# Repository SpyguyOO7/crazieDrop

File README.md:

# PCB for little electromagnet drop mech
## SChematic

## Model + Layout

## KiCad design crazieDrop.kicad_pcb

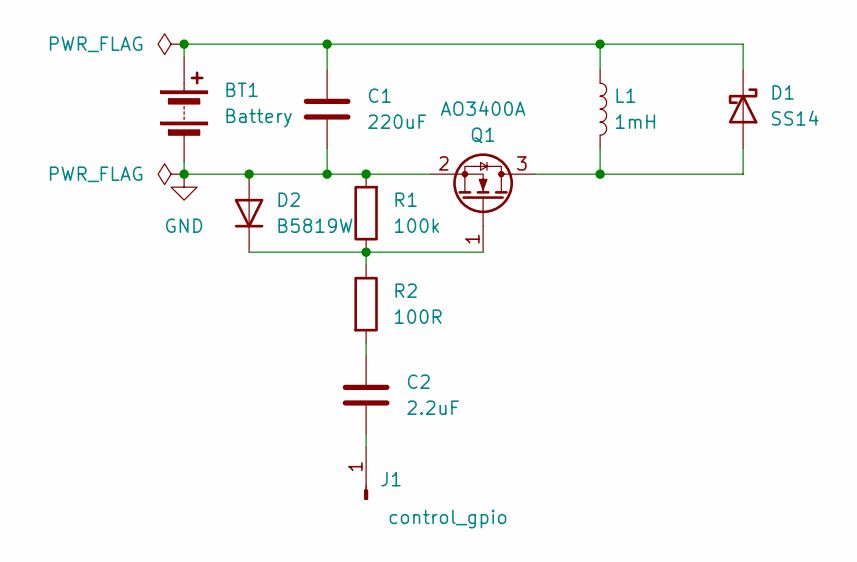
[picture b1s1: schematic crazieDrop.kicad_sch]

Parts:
BT1: Battery; PinHeader_1x02_P2.54mm_Vertical
C1: 220uF; CP_Elec_6.3x7.7; LCSC C2827940
C2: 2.2uF; C_0603_1608Metric; LCSC C23630
D1: SS14; D_SMA_Handsoldering; LCSC C2480
D2: B5819W; D_SOD-123; LCSC C8598
J1: control_gpio; PinHeader_1x01_P2.54mm_Vertical
L1: 1mH; PinHeader_1x02_P2.54mm_Vertical
Q1: AO3400A; SOT-23_Handsoldering; LCSC C20917
R1: 100k; R_0603_1608Metric; LCSC C25803
R2: 100R; R_0603_1608Metric; LCSC C22775

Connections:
GND: BT1.2 (-), C1.2, D2.2 (A), Q1.2 (S), R1.2
unnamed: BT1.1 (+), C1.1, D1.1 (K), L1.1
unnamed: C2.1, R2.2
unnamed: D1.2 (A), L1.2, Q1.3 (D)
unnamed: D2.1 (K), Q1.1 (G), R1.1, R2.1
unnamed: C2.2, J1.1 (Pin_1_1)

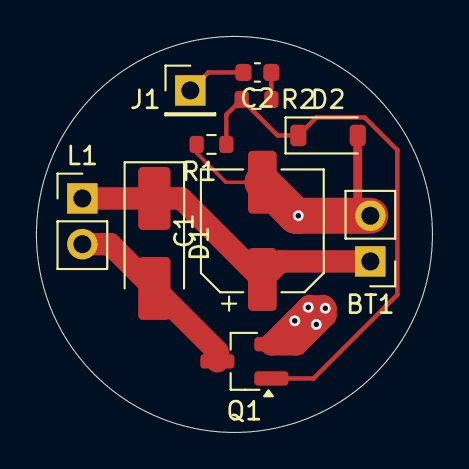
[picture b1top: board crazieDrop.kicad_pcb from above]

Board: 2 copper layers, 22.0 x 22.0 mm, 10 parts (0 on the bottom side), 6 nets.

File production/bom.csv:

Designator,Footprint,Quantity,Value,LCSC Part #
BT1,PinHeader_1x02_P2.54mm_Vertical,1,Battery,
C1,CP_Elec_6.3x7.7,1,220uF,C2827940
C2,0603,1,2.2uF,C23630
D1,D_SMA_Handsoldering,1,SS14,C2480
D2,D_SOD-123,1,B5819W,C8598
J1,PinHeader_1x01_P2.54mm_Vertical,1,control_gpio,
L1,PinHeader_1x02_P2.54mm_Vertical,1,1mH,
Q1,SOT-23_Handsoldering,1,AO3400A,C20917
R1,0603,1,100k,C25803
R2,0603,1,100R,C22775
